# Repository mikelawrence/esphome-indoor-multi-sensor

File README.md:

# ESPHome Indoor Multi-Sensor

<p align="center">

</p>

There are a lot of presence sensors using a combination of PIR and High Frequency Radar Human Presence Detectors to get a combination of quick response and low movement detection like when sleeping. Good examples of these types of sensor are the [Everything Presence One](https://shop.everythingsmart.io/products/everything-presence-one-kit) and [Roomsense IQ](https://www.roomsenselabs.com/). The later has a sensor module that you can add to support all sorts readings like Particular Matter (PM) Carbon Monoxide. But since I like to do everything myself. I started thinking about how I would approach this and more specifically what sensors did I want.

I settled on the following characteristics:

* ESP32-S3
* ESPHome software development
* USB-C Power
* Multiple options for Radar presence detection modules
  - Hi-Link LD2410B
  - Hi-Link LD2450
  - DFRobot C4001 (SEN609 and SEN610)
* PIR (Panasonic)
* Sensirion SEN66 All-in-One (Package A)
  - Temperature
  - Humidity
  - Particulate Matter (PM)
  - CO₂
  - Volatile Organic Compound (VOC)
  - Nitrogen Oxide (NOX)
* Or individual Sensors (Package B)
  - Sensirion SHT4X Temperature and Humidity
  - Sensirion SCD4X CO₂
  - Sensirion SGP4X VOC and NOX
* Bosch BMP581 Pressure
* Figaro TGS5141 Carbon Monoxide (CO)
* AMS TSL2591 Light
* Microphone for sound levels
* A Speaker for alerts
* INA228 Power and Energy Monitor

## Status
* **Rev -** Has been fabricated and tested. I had JLCPCB fabricate the boards and I self assembled using a Home-Brew reflow oven by [Whizoo Controleo3](https://whizoo.com/). All circuits have been tested and found to be operational. 
* **Rev A** There was an issue with signal integrity on the I2C bus when communicating with the SEN66. To fix the problem I added stronger pullups and a new and dedicated I2C bus to the SEN66. Thus Rev A was born. I have not fabricate Rev A boards since I still have 6 Rev - boards but the changes are minor and should be fine. Please let me know if you built Rev A and how it went. 

## Design Decisions
### ESP32 and ESPHome
ESPHome is closely aligned with Home Assistant. In fact they are the same company. Home Assistant uses ESPHome for some of their hardware like the [Home Assistant Voice Preview Edition](https://www.home-assistant.io/voice-pe/) or [Bluetooth Proxy](https://esphome.io/components/bluetooth_proxy.html). I chose a newer ESP32-S3 for this design which also has Bluetooth support.

This project uses ESP32-S3-WROOM-2-N32R16V which has an enormous 32MB of flash and 16MB of octal PSRAM. These specs are way out of the normal range for an ESP32, so why? First I wanted to be able to store sounds directly on the unit itself mainly so it can sound out alerts even if Home Assistant is not connected. The PSRAM came along with the big Flash but it also has benefits. Sound pressure analysis likes more PSRAM and so does Bluetooth Proxying.

### Sensors
#### Radar based Human Presence Sensors
Both the Hi-Link sensors (LS2410B and LD2450) are supported by ESPHome directly but the DFRobot C4001 is not. I wrote an ESPHome External Component available [here](https://github.com/mikelawrence/ESPHome-Components?tab=readme-ov-file#esphome-c4001-external-component). The board has the LD2410 and LD2450 sharing the same physical space but the DFRobot C4001 can exist next to one of the LD sensors. I added circuitry so that you can choose which sensor to operate electrically. However enabling both simultaneously could result in strange behavior. After using the LD2450 for  bit I realized the the "just released" LD2450 ESPHome component has some short comings. Specifically there is no installation angle or flip-x-axis. So I added them in my version of the LD2450 ESPHome component [here] (https://github.com/mikelawrence/ESPHome-Components?tab=readme-ov-file#esphome-ld2450-external-component).

#### Sensor choices
The [SEN66](https://sensirion.com/products/catalog/SEN66) may be an expensive sensor package but it does it all, Temperature, Humidity, PM, CO₂, VOC and NOX. A tiny fan is primarily used for measuring PM but it also moves air by the temperature and humidity sensors making them fairly responsive. I call this Package A. If you choose not use the SEN66 you can populate the Package B individual sensors ([SHT4X](https://sensirion.com/media/documents/33FD6951/67EB9032/HT_DS_Datasheet_SHT4x_5.pdf), [SCD4X](https://sensirion.com/media/documents/48C4B7FB/67FE0194/CD_DS_SCD4x_Datasheet_D1.pdf) and [SGP4X](https://sensirion.com/media/documents/A056FE9C/61E970C2/Sensirion_Flyer_Gas_Sensors_Web.pdf)) to get Temperature, Humidity, CO₂, VOC and NOX. The only thing missing is PM.

#### Carbon Monoxide
For some reason CO sensors are not as common as CO₂ sensors. Most are expensive and have short life spans. The  Figaro TGS5141 is inexpensive and has a 10-year life span but it isn't a nice all-in-one with I2C interface. You have to add a transimpedance amplifier and then digitize the analog signal. I chose to add an ADS1115 16-bit ADC right next to the transimpedance amplifier instead of running analog signal across the board to the questionable ESP32 built in ADC. The ADS1115 also a has true differential Programmable Gain Amplifier on the input. This reduces the CO sensor circuit complexity. This sensor is not going to be very accurate but detection of CO in even low levels is probably a reason for concern. So even if not a safety sensor it can help.

I verified the CO circuit using CO Bump Gas. It doesn't calibrate, but it will prove that the sensor responds to the presence of CO. I used a small upside down container on my outside bench with the sensor I wanted to test inside. Squirting some bump gas inside with the thin straw showed that 4 out of 5 sensors responded to the gas. The 5'th that didn't respond had a solder bridge between two pins on the transimpedance amplifier. A quick removal of the solder bridge fixed the non-functioning sensor.

> [!WARNING]
> This CO sensor is not rated for safety nor is it particularly accurate. Use at your own risk! I still have UL listed (American) CO detectors as my main line of defense.

#### Pressure and Light
The [BMP581](https://www.bosch-sensortec.com/media/boschsensortec/downloads/datasheets/bst-bmp581-ds004.pdf) pressure sensor is primarily used as a barometric pressure sensor but it is sensitive enough for micro-pressure changes like when a door is closed. Pressure can also be used to compensate the CO₂ sensor in either the SEN6X or the SCD4X. Light is another measurement that may or may not be helpful but I included it. Keep in mind that this measurement is inside an enclosure thus has some significant limitations when it comes to accuracy.

#### Speaker and Microphone
The SEN66 takes up a lot of space so a small speaker is necessary. I choose a flat speaker from [Same Sky](https://www.sameskydevices.com/product/audio/speakers/miniature-(10-mm~40-mm)/cms-251437-24sp-x8) and started playing. My first attempts were pretty, flat, meaning these small speakers don't move a lot of air and in free space they have almost no volume. After doing some research it became clear, the speaker needs a enclosure. I was able to come up with a small 3D printed enclosure attached to the PCB itself. Man what a difference. This 2W speaker kicks some serious butt.

I threw in the microphone to measure sound levels. The intent is listen for noise as additional presence detection.

#### Power and Energy Monitor
The [INA228](https://www.ti.com/lit/ds/symlink/ina228.pdf) power and energy monitor can give instantaneous readings of voltage, current and power but it also measures energy over time (WHr). 

### USB-C Power
I'm not using USB-C Power Delivery but I am expecting 5V @ 3A which is readily available if you have the right USB-C Power Brick. The PCB has the appropriate resistors on the CC pins which will request 5V @ 3A from a standard USB-C Power Brick. Testing shows slightly less than 1W for the Package A version and slightly less than 0.9 W for the Package B option as measured by the INA228. Quick measurements show about 8.1kWh/yr for Package A and 7.3kWh/yr for Package B. In Texas that is less than $1 per year.

## Enclosure
<p align="center">
  
</p>

More information is in the enclosure [README](enclosure/README.md) file.

## Operation
Expect an ESPHome YAML configuration soon.

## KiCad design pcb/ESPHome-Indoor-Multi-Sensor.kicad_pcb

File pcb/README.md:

# ESPHome Indoor Multi-Sensor PCB
<p align="center">
     <br />
    3D Render of ESPHome Indoor Multi-Sensor PCB
</p>

The PCB is designed in [KiCad](https://www.kicad.org/). Fabrication and is tuned toward [JCLPCB](https://jlcpcb.com/). The production folder has everything you need for JLCPCB to send you ready to assemble boards. I chose not to use JLCPCB for assembly because they had a hard time with some the parts I chose for this design. When I had the boards fabricated I also had them panelize two PCBs and produce a stencil for both for the panelized boards.

## Schematic
<p align="center">
     <br />
    Schematic
</p>

### Do Not Populate (DNP) Notes
When you use the SEN66 from Sensirion you don't need to install discrete sensor components. ```U11```, ```U12```, ```U16```, ```C29```, ```C29```, ```C30```, ```C31```, ```C43```
* ```C9```, ```C10```, ```R16``` and ```R17```: These components are an optional snubber used to reduce EMI. Not needed.

## Bill of Materials
<p align="center">
     <br />
    Interactive BOM
</p>

## PCB Info
* 4 layer to support an additional ground plane and signal layer to reduce plane interruptions on the outer layers.
* There has been an attempt thermally isolate the SHT4X Temperature and Humidity Sensor but there are no guarantees.
* Dimensions are 52.5mm X 59.7mm.
* Requires oven reflow or hot air to assemble most components.

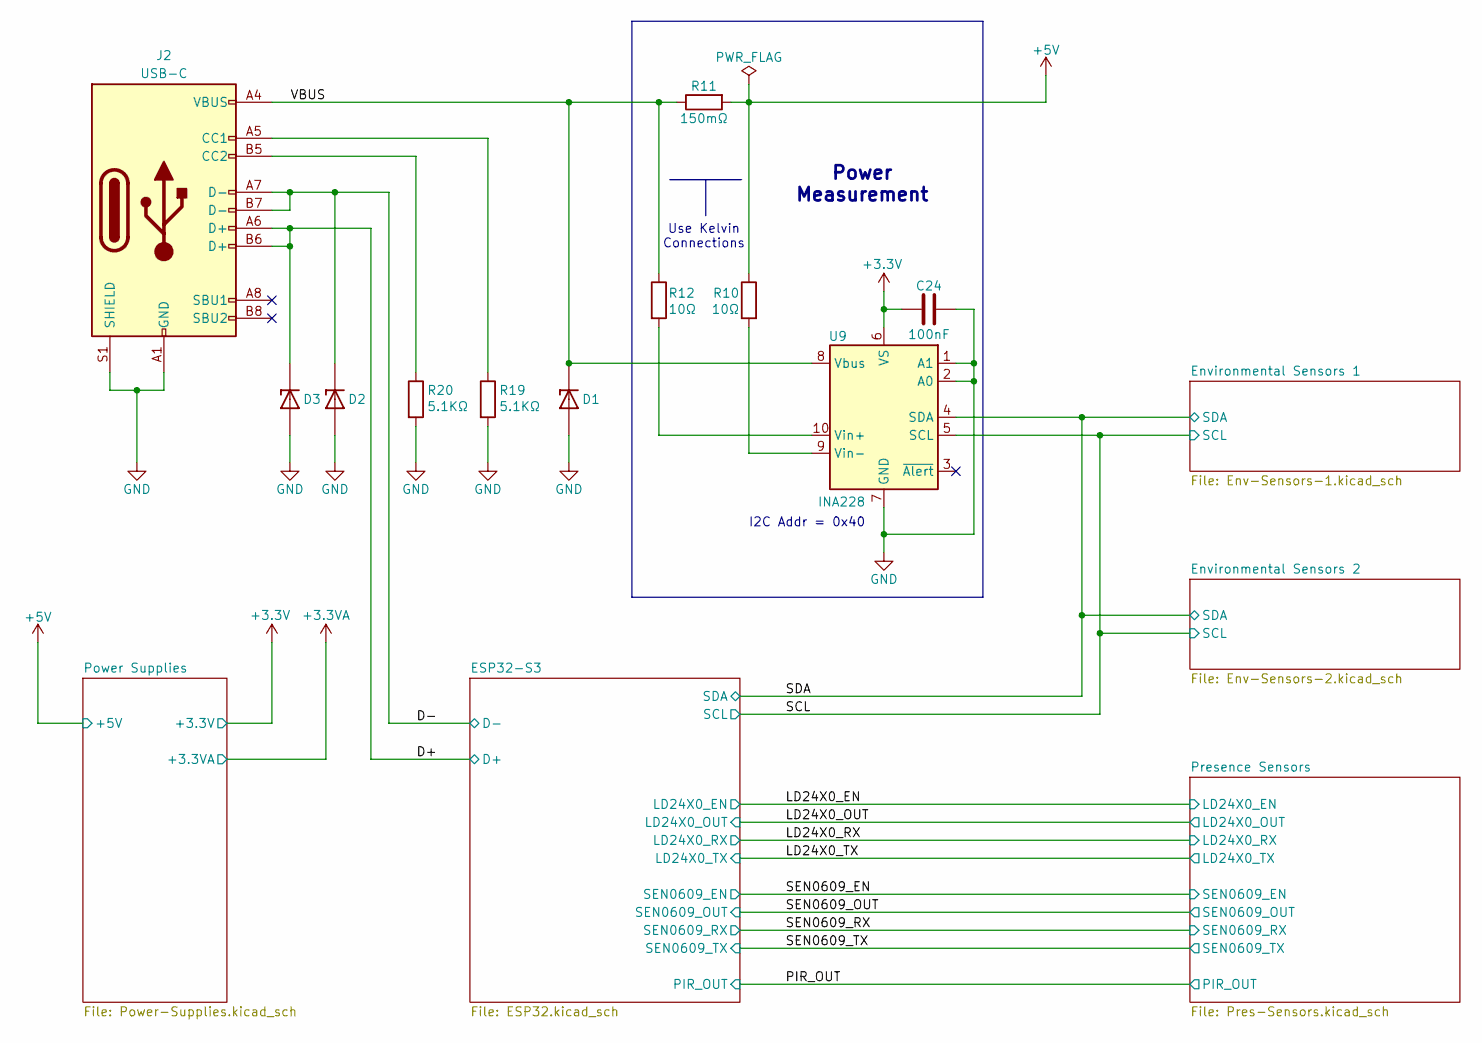
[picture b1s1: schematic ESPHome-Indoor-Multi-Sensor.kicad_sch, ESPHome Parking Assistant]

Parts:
C24: 100nF; C_0402_1005Metric; Part Number CL05B104KB54PNC
D1, D2, D3: ESDA8P80-1U1M; TVS_ESDA25P35-1U1M; Part Number ESDA8P80-1U1M
J2: USB-C; USB_C_Receptacle_HRO_TYPE-C-31-M-12; Part Number 1332645
R10, R12: 10Ω; R_0402_1005Metric; Part Number CRCW040210R0FKEE
R11: 150mΩ; R_1210_3225Metric; Part Number ERJ-14BSFR15U
R19, R20: 5.1KΩ; R_0402_1005Metric; Part Number CRCW04025K10FKED
U9: INA228; VSSOP-10_3x3mm_P0.5mm; Part Number INA228AIDGSR

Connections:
+3.3V: C24.2, U9.6 (VS); also elsewhere on the board
+5V: R10.1, R11.2; also elsewhere on the board
/D+: D3.C, J2.A6 (D+), J2.B6 (D+); also elsewhere on the board
/D-: D2.C, J2.A7 (D-), J2.B7 (D-); also elsewhere on the board
/SCL: U9.5 (SCL); also elsewhere on the board
/SDA: U9.4 (SDA); also elsewhere on the board
/VBUS: D1.C, J2.A4 (VBUS), J2.A9 (VBUS), J2.B4 (VBUS), J2.B9 (VBUS), R11.1, R12.1, U9.8 (Vbus)
GND: C24.1, D1.A, D2.A, D3.A, J2.A1 (GND), J2.A12 (GND), J2.B1 (GND), J2.B12 (GND), J2.S1 (SHIELD), R19.2, R20.2, U9.1 (A1), U9.2 (A0), U9.7 (GND); also elsewhere on the board
unnamed: J2.A5 (CC1), R19.1
unnamed: J2.B5 (CC2), R20.1
unnamed: R12.2, U9.10 (Vin+)
unnamed: R10.2, U9.9 (Vin-)

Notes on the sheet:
I2C Addr = 0x40
Power Measurement
Use Kelvin Connections

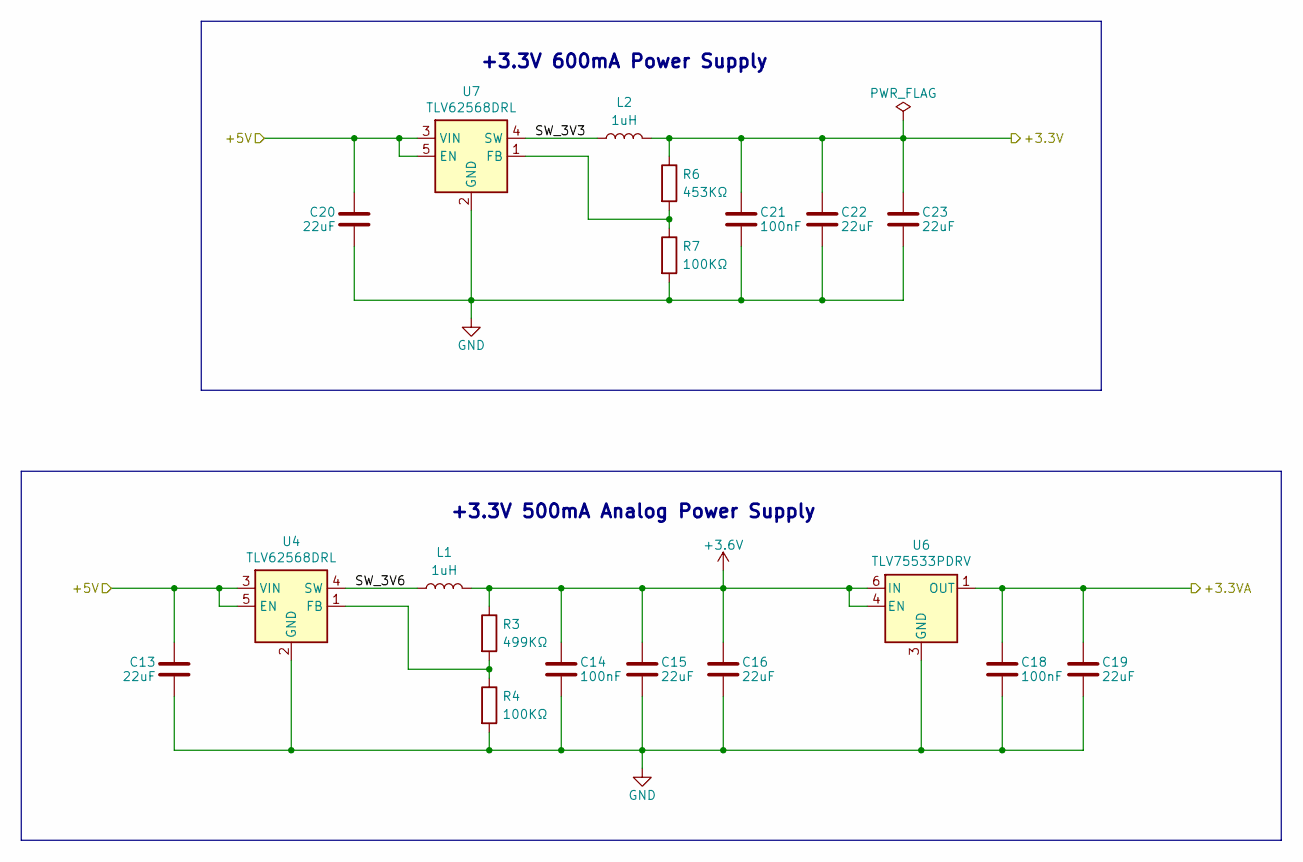
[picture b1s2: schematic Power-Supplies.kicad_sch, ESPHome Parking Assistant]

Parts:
C13, C15, C16, C19, C20, C22, C23: 22uF; C_0603_1608Metric; Part Number GRM188R60J226MEA0D
C14, C18, C21: 100nF; C_0402_1005Metric; Part Number CL05B104KB54PNC
L1, L2: 1uH; L_1008_2520Metric; Part Number DFE252012F-1R0M=P2
R3: 499KΩ; R_0402_1005Metric; Part Number CRCW0402499KFKED
R4, R7: 100KΩ; R_0402_1005Metric; Part Number CRCW0402100KFKED
R6: 453KΩ; R_0402_1005Metric; Part Number CRCW0402453KFKED
U4, U7: TLV62568DRL; SOT50P160X60-6N; Part Number TLV62568DRL
U6: TLV75533PDRV; VREG_TLV75533PDRVR; Part Number TLV75533PDRV

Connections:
+3.3V: C21.2, C22.1, C23.1, L2.2, R6.1; also elsewhere on the board
+3.3VA: C18.2, C19.1, U6.1 (OUT); also elsewhere on the board
+3.6V: C14.2, C15.1, C16.1, L1.2, R3.1, U6.4 (EN), U6.6 (IN)
+5V: C13.1, C20.1, U4.3 (VIN), U4.5 (EN), U7.3 (VIN), U7.5 (EN); also elsewhere on the board
/Power Supplies/SW_3V3: L2.1, U7.4 (SW)
/Power Supplies/SW_3V6: L1.1, U4.4 (SW)
GND: C13.2, C14.1, C15.2, C16.2, C18.1, C19.2, C20.2, C21.1, C22.2, C23.2, R4.2, R7.2, U4.2 (GND), U6.3 (GND), U6.7 (GND), U7.2 (GND); also elsewhere on the board
unnamed: R3.2, R4.1, U4.1 (FB)
unnamed: R6.2, R7.1, U7.1 (FB)

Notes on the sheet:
+3.3V 600mA Power Supply
+3.3V 500mA Analog Power Supply

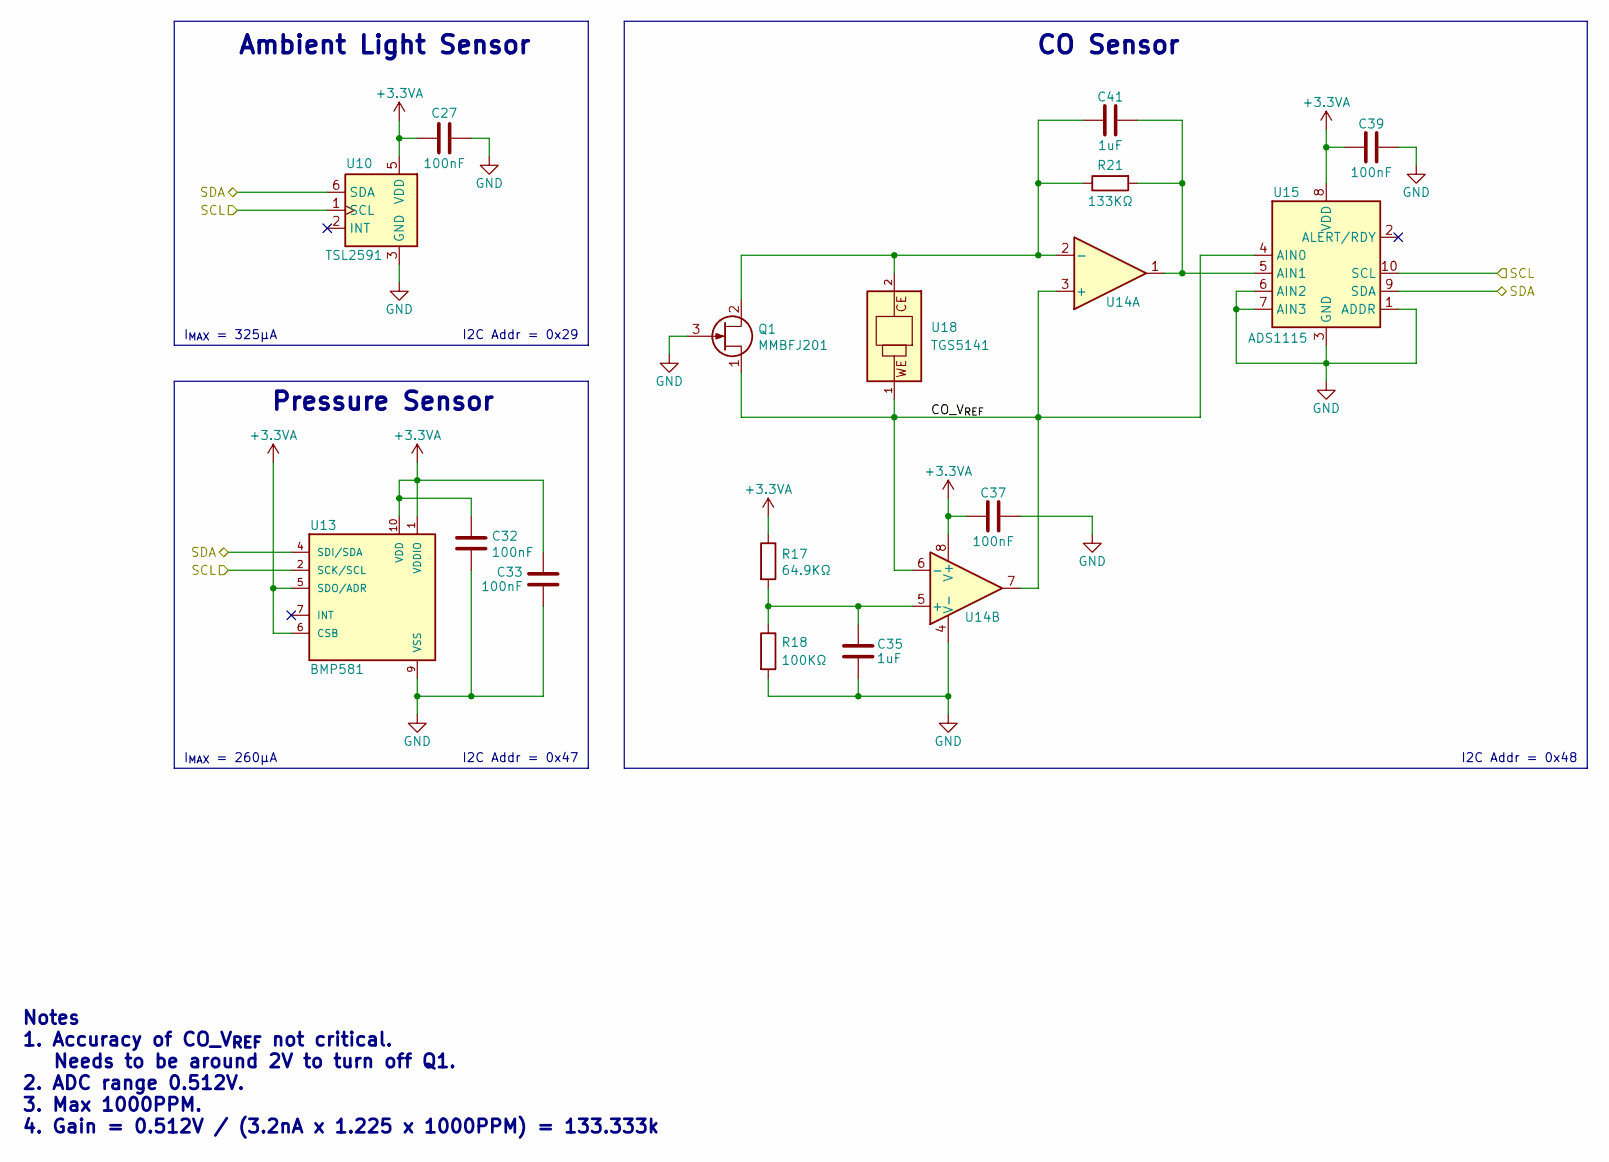
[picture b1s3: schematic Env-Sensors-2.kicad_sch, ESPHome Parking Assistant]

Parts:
C27, C32, C33, C37, C39: 100nF; C_0402_1005Metric; Part Number CL05B104KB54PNC
C35, C41: 1uF; C_0402_1005Metric; Part Number CL05A105KA5NQNC
Q1: MMBFJ201; SOT-23; Part Number MMBFJ201
R17: 64.9KΩ; R_0402_1005Metric; Part Number CRCW040264K9FKED
R18: 100KΩ; R_0402_1005Metric; Part Number CRCW0402100KFKED
R21: 133KΩ; R_0402_1005Metric; Part Number CRCW0402133KFKED
U10: TSL2591; AMS_TSL25911FN; Part Number TSL2591
U13: BMP581; Part Number BMP581
U14: MCP6042; MSOP-8_3x3mm_P0.65mm; Part Number MCP6042T-I/MS
U15: ADS1115; TSSOP-10_3x3mm_P0.5mm; Part Number ADS1115IDGS
U18: TGS5141; TGS-5141; Part Number TGS5141-P00

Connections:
+3.3VA: C27.2, C32.1, C33.1, C37.1, C39.1, R17.1, U10.5 (VDD), U13.1 (VDDIO), U13.5 (SDO/ADR), U13.6 (CSB), U13.10 (VDD), U14.8 (V+), U15.8 (VDD); also elsewhere on the board
/Environmental Sensors 2/CO_V_{REF}: Q1.1 (D), U14.3 (+), U14.6 (-), U14.7, U15.4 (AIN0), U18.1 (WE)
/SCL: U10.1 (SCL), U13.2 (SCK/SCL), U15.10 (SCL); also elsewhere on the board
/SDA: U10.6 (SDA), U13.4 (SDI/SDA), U15.9 (SDA); also elsewhere on the board
GND: C27.1, C32.2, C33.2, C35.2, C37.2, C39.2, Q1.3 (G), R18.2, U10.3 (GND), U13.3 (VSS), U13.8 (VSS), U13.9 (VSS), U14.4 (V-), U15.1 (ADDR), U15.3 (GND), U15.6 (AIN2), U15.7 (AIN3); also elsewhere on the board
unnamed: C41.1, Q1.2 (S), R21.1, U14.2 (-), U18.2 (CE)
unnamed: C35.1, R17.2, R18.1, U14.5 (+)
unnamed: C41.2, R21.2, U14.1, U15.5 (AIN1)

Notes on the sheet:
I_{MAX} = 260µA
CO Sensor
I2C Addr = 0x29
I2C Addr = 0x48
Notes 1. Accuracy of CO_V_{REF} not critical. Needs to be around 2V to turn off Q1. 2. ADC range 0.512V. 3. Max 1000PPM. 4. Gain = 0.512V / (3.2nA x 1.225 x 1000PPM) = 133.333k
Ambient Light Sensor
I_{MAX} = 325µA
I2C Addr = 0x47
Pressure Sensor

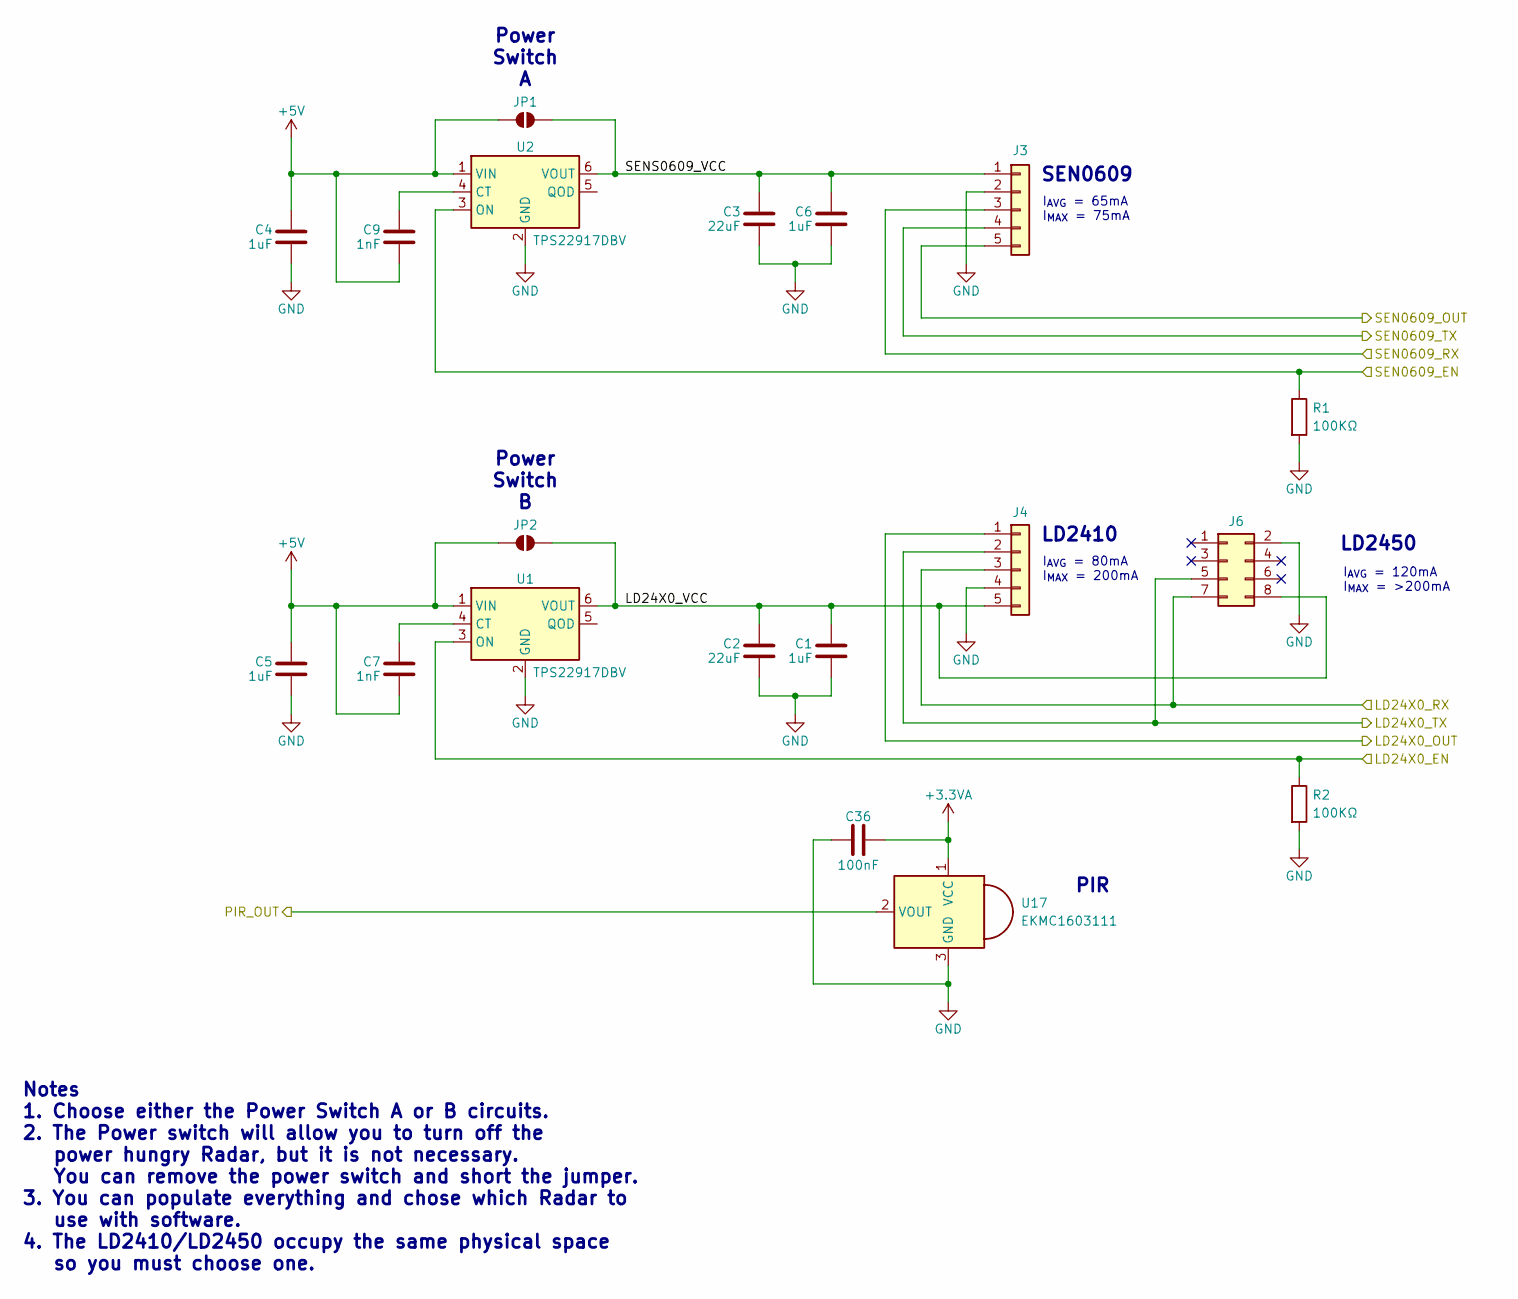
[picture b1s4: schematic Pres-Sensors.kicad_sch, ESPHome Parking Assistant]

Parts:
C1, C4, C5, C6: 1uF; C_0402_1005Metric; Part Number CL05A105KA5NQNC
C2, C3: 22uF; C_0603_1608Metric; Part Number GRM188R60J226MEA0D
C7, C9: 1nF; C_0402_1005Metric; Part Number 04023C102KAT2A
C36: 100nF; C_0402_1005Metric; Part Number CL05B104KB54PNC
J3: SEN0609; PinHeader_1x05_P2.54mm_Vertical; Part Number CES-105-01-T-S
J4: LD2410; PinSocket_1x05_P1.27mm_Vertical_SMD_Pin1Right; Part Number RSM-105-02-S-S
J6: LD2450; PinSocket_2x04_P2.00mm_Vertical_SMD; Part Number 79109-1003
JP1, JP2: SolderJumper-2_P1.3mm_Open_RoundedPad1.0x1.5mm
R1, R2: 100KΩ; R_0402_1005Metric; Part Number CRCW0402100KFKED
U1, U2: TPS22917DBV; SOT-23-6; Part Number TPS22917DBV
U17: EKMC1603111; EKMC163111; Part Number EKMC1603111

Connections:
+3.3VA: C36.2, U17.1 (VCC); also elsewhere on the board
+5V: C4.1, C5.1, C7.2, C9.2, JP1.1 (A), JP2.1 (A), U1.1 (VIN), U2.1 (VIN); also elsewhere on the board
/LD24X0_EN: R2.1, U1.3 (ON); also elsewhere on the board
/LD24X0_OUT: J4.1; also elsewhere on the board
/LD24X0_RX: J4.3, J6.7; also elsewhere on the board
/LD24X0_TX: J4.2, J6.5; also elsewhere on the board
/PIR_OUT: U17.2 (VOUT); also elsewhere on the board
/Presence Sensors/LD24X0_VCC: C1.1, C2.1, J4.5, J6.8, JP2.2 (B), U1.6 (VOUT)
/Presence Sensors/SENS0609_VCC: C3.1, C6.1, J3.1, JP1.2 (B), U2.6 (VOUT)
/SEN0609_EN: R1.1, U2.3 (ON); also elsewhere on the board
/SEN0609_OUT: J3.5; also elsewhere on the board
/SEN0609_RX: J3.3; also elsewhere on the board
/SEN0609_TX: J3.4; also elsewhere on the board
GND: C1.2, C2.2, C3.2, C4.2, C5.2, C6.2, C36.1, J3.2, J4.4, J6.2, R1.2, R2.2, U1.2 (GND), U2.2 (GND), U17.3 (GND); also elsewhere on the board
unnamed: C7.1, U1.4 (CT)
unnamed: C9.1, U2.4 (CT)

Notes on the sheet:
Power Switch B
Power Switch A
I_{AVG} = 65mA I_{MAX} = 75mA
LD2450
LD2410
I_{AVG} = 80mA I_{MAX} = 200mA
PIR
SEN0609
Notes 1. Choose either the Power Switch A or B circuits. 2. The Power switch will allow you to turn off the power hungry Radar, but it is not necessary. You can remove the power switch and short the jumper. 3. You can populate everything and chose which Radar to use with software. 4. The LD2410/LD2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
I_{AVG} = 120mA I_{MAX} = >200mA

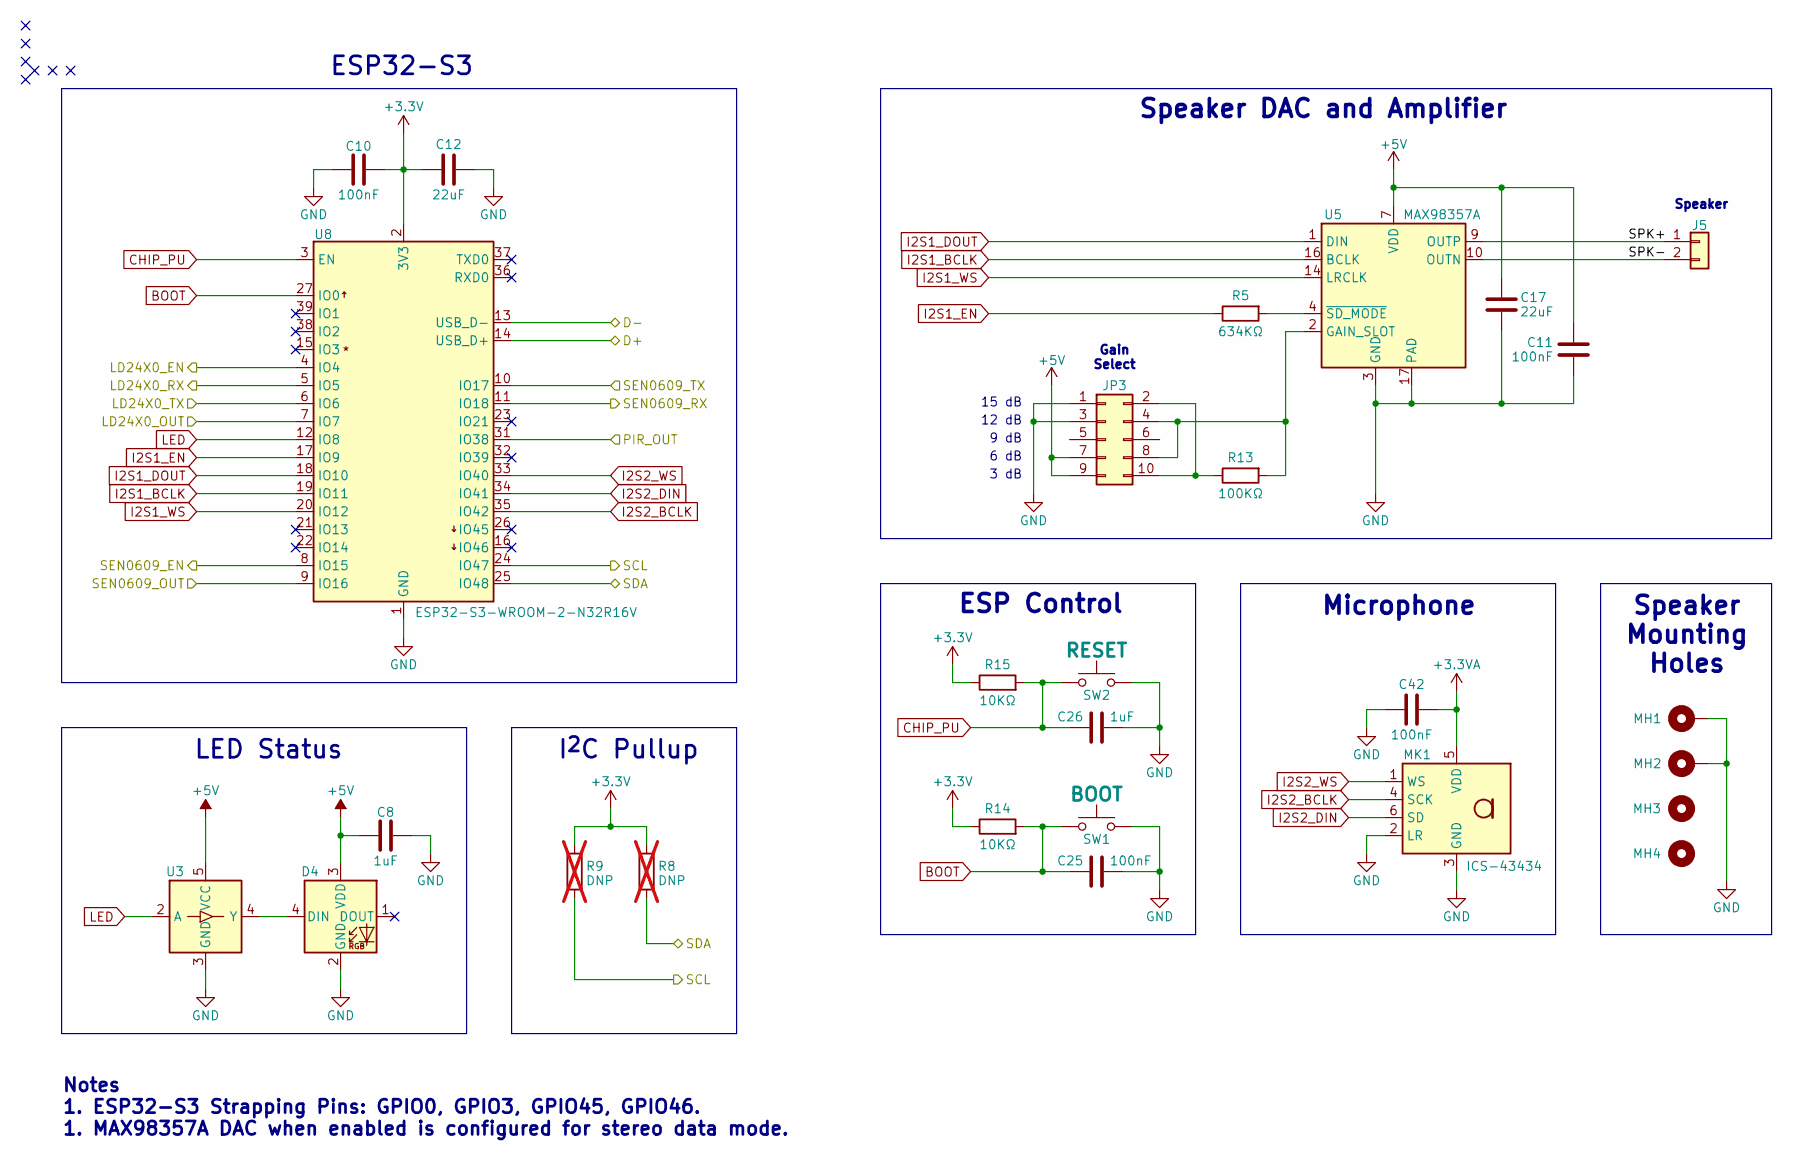
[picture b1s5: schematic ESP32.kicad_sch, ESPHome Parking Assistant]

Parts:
C8, C26: 1uF; C_0402_1005Metric; Part Number CL05A105KA5NQNC
C10, C11, C25, C42: 100nF; C_0402_1005Metric; Part Number CL05B104KB54PNC
C12, C17: 22uF; C_0603_1608Metric; Part Number GRM188R60J226MEA0D
D4: NeoPixel_THT; LED_D5.0mm-4_RGB; Part Number 1938
J5: SPKR; PinHeader_1x02_P2.00mm_Vertical; Part Number CMS-251437-24SP-X8
JP3: Gain; SAMTEC_TMM-105-01-X-D-SM; Part Number TMM-105-01-L-D-SM-P-TR
MH1, MH2, MH3, MH4: MountingHole_2.2mm_M2_Pad
MK1: ICS-43434; InvenSense_ICS-43434-6_3.5x2.65mm; Part Number ICS-43434
R5: 634KΩ; R_0402_1005Metric; Part Number CRCW0402634KFKED
R8, R9: DNP; R_0402_1005Metric; not fitted
R13: 100KΩ; R_0402_1005Metric; Part Number CRCW0402100KFKED
R14, R15: 10KΩ; R_0402_1005Metric; Part Number CRCW040210K0FKED
SW1: BOOT; SW_SPST_B3U-1000P-B; Part Number B3U-1000P
SW2: RESET; SW_SPST_B3U-1000P-B; Part Number B3U-1000P
U3: SN74LV1T34DBV; SOT-23-5; Part Number SN74LV1T34DBV
U5: MAX98357A; TQFN-16-1EP_3x3mm_P0.5mm_EP1.23x1.23mm; Part Number MAX98357AETE
U8: ESP32-S3-WROOM-2-N32R16V; ESP32-S3-WROOM-2; Part Number ESP32-S3-WROOM-2-N32R16V

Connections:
+3.3V: C10.2, C12.1, R8.1, R9.1, R14.1, R15.1, U8.2 (3V3); also elsewhere on the board
+3.3VA: C42.2, MK1.5 (VDD); also elsewhere on the board
+5V: C8.1, C11.1, C17.1, D4.3 (VDD), JP3.7, JP3.9, U3.5 (VCC), U5.7 (VDD), U5.8 (VDD); also elsewhere on the board
/D+: U8.14 (USB_D+); also elsewhere on the board
/D-: U8.13 (USB_D-); also elsewhere on the board
/ESP32-S3/SPK+: J5.1, U5.9 (OUTP)
/ESP32-S3/SPK-: J5.2, U5.10 (OUTN)
/LD24X0_EN: U8.4 (IO4); also elsewhere on the board
/LD24X0_OUT: U8.7 (IO7); also elsewhere on the board
/LD24X0_RX: U8.5 (IO5); also elsewhere on the board
/LD24X0_TX: U8.6 (IO6); also elsewhere on the board
/PIR_OUT: U8.31 (IO38); also elsewhere on the board
/SCL: R9.2, U8.24 (IO47); also elsewhere on the board
/SDA: R8.2, U8.25 (IO48); also elsewhere on the board
/SEN0609_EN: U8.8 (IO15); also elsewhere on the board
/SEN0609_OUT: U8.9 (IO16); also elsewhere on the board
/SEN0609_RX: U8.11 (IO18); also elsewhere on the board
/SEN0609_TX: U8.10 (IO17); also elsewhere on the board
BOOT: C25.2, R14.2, SW1.2, U8.27 (IO0)
CHIP_PU: C26.1, R15.2, SW2.2, U8.3 (EN)
GND: C8.2, C10.1, C11.2, C12.2, C17.2, C25.1, C26.2, C42.1, D4.2 (GND), JP3.1, JP3.3, MH1.1, MH2.1, MK1.2 (LR), MK1.3 (GND), SW1.1, SW2.1, U3.3 (GND), U5.3 (GND), U5.11 (GND), U5.15 (GND), U5.17 (PAD), U8.1 (GND), U8.40 (GND), U8.41 (GND); also elsewhere on the board
I2S1_BCLK: U5.16 (BCLK), U8.19 (IO11)
I2S1_DOUT: U5.1 (DIN), U8.18 (IO10)
I2S1_EN: R5.1, U8.17 (IO9)
I2S1_WS: U5.14 (LRCLK), U8.20 (IO12)
I2S2_BCLK: MK1.4 (SCK), U8.35 (IO42)
I2S2_DIN: MK1.6 (SD), U8.34 (IO41)
I2S2_WS: MK1.1 (WS), U8.33 (IO40)
LED: U3.2 (A), U8.12 (IO8)
unnamed: D4.4 (DIN), U3.4 (Y)
unnamed: JP3.4, JP3.8, R13.2, U5.2 (GAIN_SLOT)
unnamed: JP3.2, JP3.10, R13.1
unnamed: R5.2, U5.4 (~SD_MODE)

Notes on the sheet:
12 dB
3 dB
Speaker
Gain Select
I^{2}C Pullup
9 dB
15 dB
ESP32-S3
6 dB
Speaker Mounting Holes
Notes 1. ESP32-S3 Strapping Pins: GPIO0, GPIO3, GPIO45, GPIO46. 1. MAX98357A DAC when enabled is configured for stereo data mode.
Speaker DAC and Amplifier
ESP Control
Microphone
LED Status

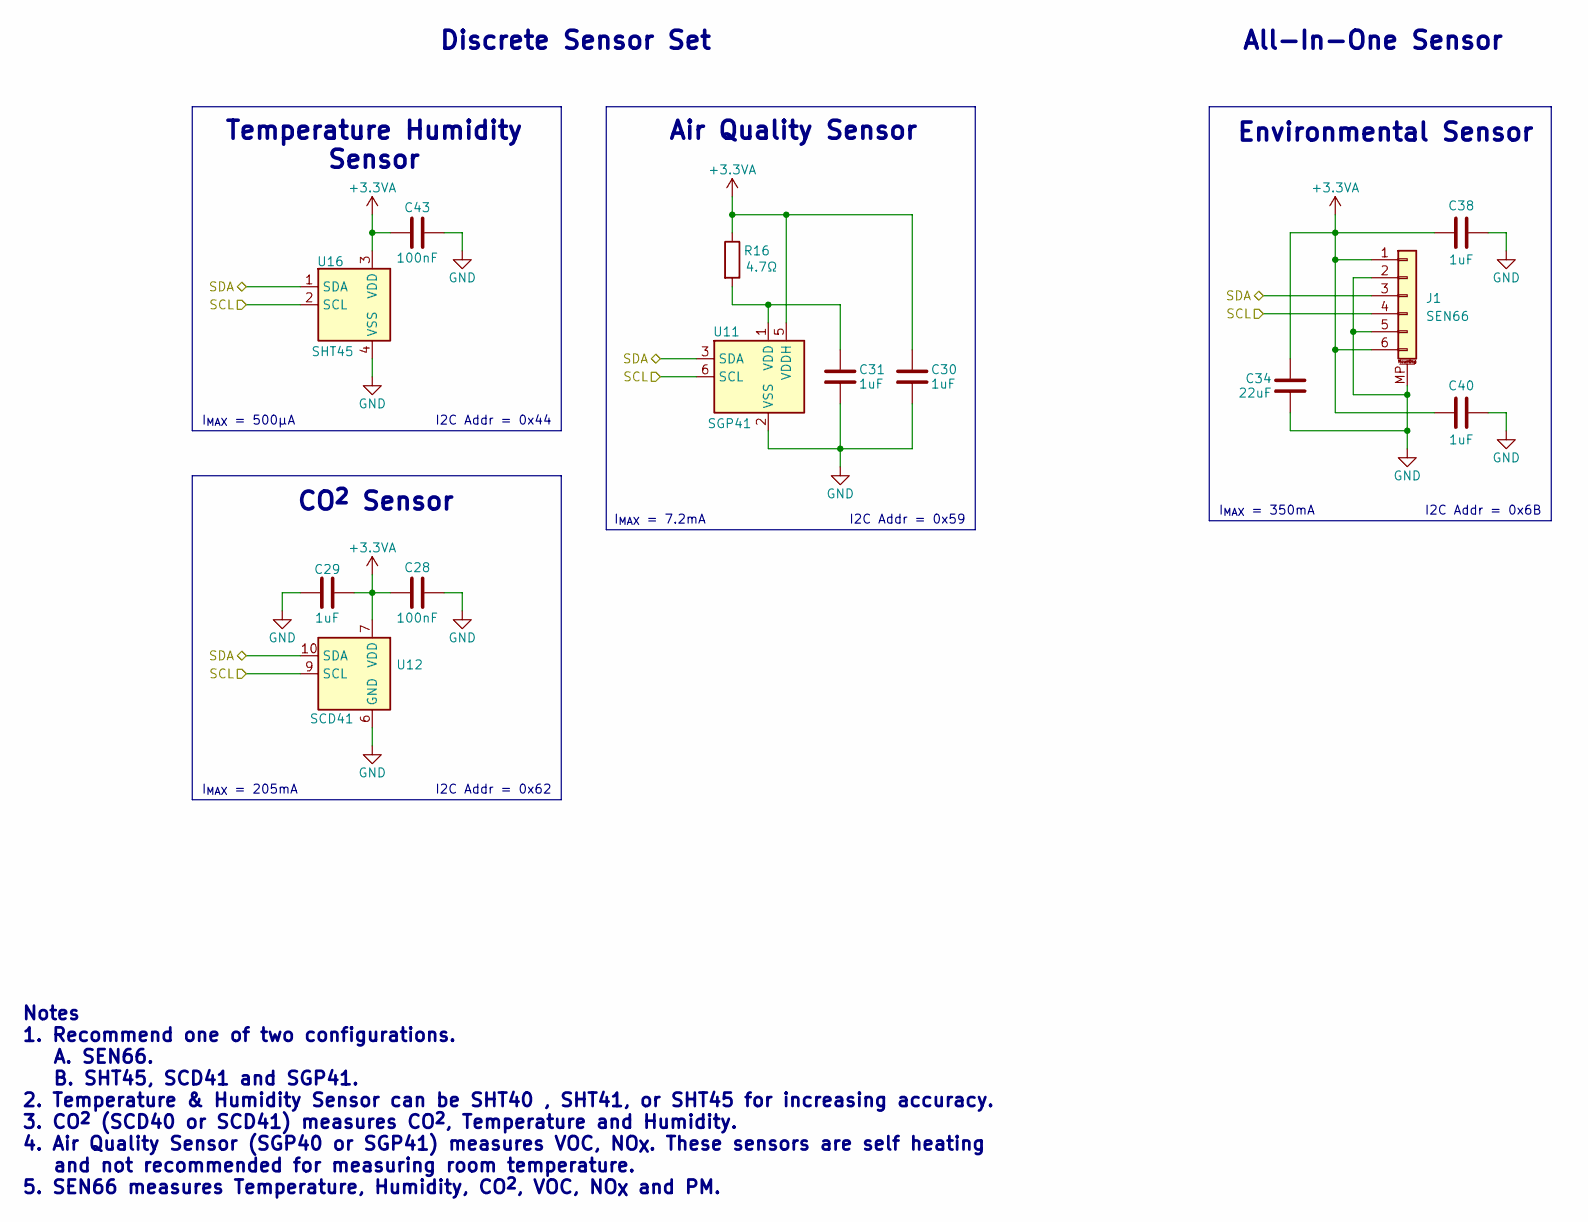
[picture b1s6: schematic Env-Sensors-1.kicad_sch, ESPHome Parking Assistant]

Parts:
C28, C43: 100nF; C_0402_1005Metric; Part Number CL05B104KB54PNC
C29, C30, C31, C38, C40: 1uF; C_0402_1005Metric; Part Number CL05A105KA5NQNC
C34: 22uF; C_0603_1608Metric; Part Number GRM188R60J226MEA0D
J1: SEN66; JST_GH_BM06B-GHS-TBT_1x06-1MP_P1.25mm_Vertical; Part Number BM06B-GHS-TBT
R16: 4.7Ω; R_0402_1005Metric; Part Number CRCW04024R70FKED
U11: SGP41; XCDR_SGP40-D-R4; Part Number SGP41-D-R4
U12: SCD41; Sensirion_SCD4x-1EP_10.1x10.1mm_P1.25mm_EP4.8x4.8mm; Part Number SCD41-D-R2
U16: SHT45; Sensirion_DFN-4_1.5x1.5mm_P0.8mm_SHT4x_NoCentralPad; Part Number SHT45-AD1B-R2

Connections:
+3.3VA: C28.2, C29.2, C30.1, C34.1, C38.1, C40.1, C43.2, J1.1, J1.6, R16.1, U11.5 (VDDH), U12.7 (VDD), U12.19 (VDD), U16.3 (VDD); also elsewhere on the board
/SCL: J1.4, U11.6 (SCL), U12.9 (SCL), U16.2 (SCL); also elsewhere on the board
/SDA: J1.3, U11.3 (SDA), U12.10 (SDA), U16.1 (SDA); also elsewhere on the board
GND: C28.1, C29.1, C30.2, C31.2, C34.2, C38.2, C40.2, C43.1, J1.2, J1.5, J1.MP (MountPin), U11.2 (VSS), U11.4 (NA), U11.7 (EP), U12.6 (GND), U12.20 (GND), U12.21 (GND), U16.4 (VSS); also elsewhere on the board
unnamed: C31.1, R16.2, U11.1 (VDD)

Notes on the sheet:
I_{MAX} = 7.2mA
I2C Addr = 0x59
I2C Addr = 0x62
CO^{2} Sensor
Environmental Sensor
I_{MAX} = 350mA
Temperature Humidity Sensor
All-In-One Sensor
Discrete Sensor Set
I2C Addr = 0x44
I2C Addr = 0x6B
I_{MAX} = 500µA
I_{MAX} = 205mA
Notes 1. Recommend one of two configurations. A. SEN66. B. SHT45, SCD41 and SGP41. 2. Temperature & Humidity Sensor can be SHT40 , SHT41, or SHT45 for increasing accuracy. 3. CO^{2} (SCD40 or SCD41) measures CO^{2}, Temperature and Humidity. 4. Air Quality Sensor (SGP40 or SGP41) measures VOC, NO_{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
Air Quality Sensor
